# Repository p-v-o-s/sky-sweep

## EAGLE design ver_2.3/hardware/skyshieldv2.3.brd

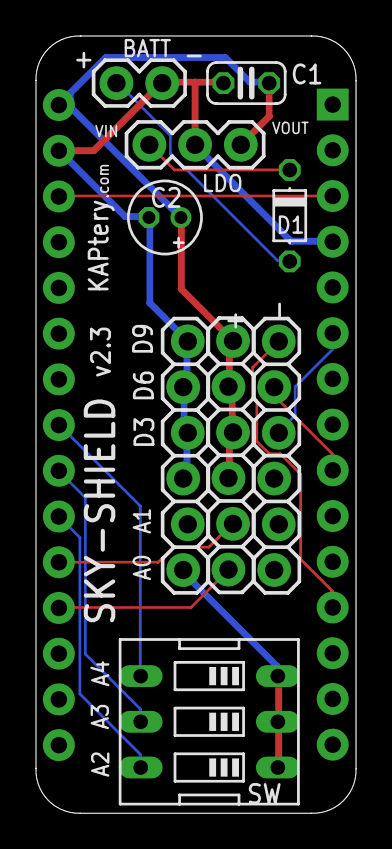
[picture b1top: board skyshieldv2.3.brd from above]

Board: 2 copper layers, 17.8 x 43.2 mm, 11 parts (0 on the bottom side), 13 nets.

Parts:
BATT: 1X02
C1: 0.1µ; C025-024X044
C2: 10µ; E1,8-4
D1: D-5
J1: HEAD15-NOSS
J2: HEAD15-NOSS-1
JP1, JP2, JP3: 1X06_LOCK
LDO-5V: LF50ABV-DG; 1X03
SW2: EDG-03

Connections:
A0: J2.12, JP2.1
A1: J2.11, JP2.2
A2: J2.10, SW2.6
A3: J2.9, SW2.5
A4: J2.8, SW2.4
D3: J1.6, JP3.4
D6: J1.9, JP3.5
D9: J1.12, JP3.6
GND: BATT.2, C1.2, C2.-, J1.4, J2.2, JP1.1, JP1.2, JP1.4, JP1.5, JP1.6, LDO-5V.2, SW2.1, SW2.2, SW2.3
unnamed: BATT.1, D1.A
unnamed: D1.C, LDO-5V.3
RESET: J1.3, J2.3
VCC: C1.1, C2.+, J2.1, JP2.4, JP2.5, JP2.6, LDO-5V.1

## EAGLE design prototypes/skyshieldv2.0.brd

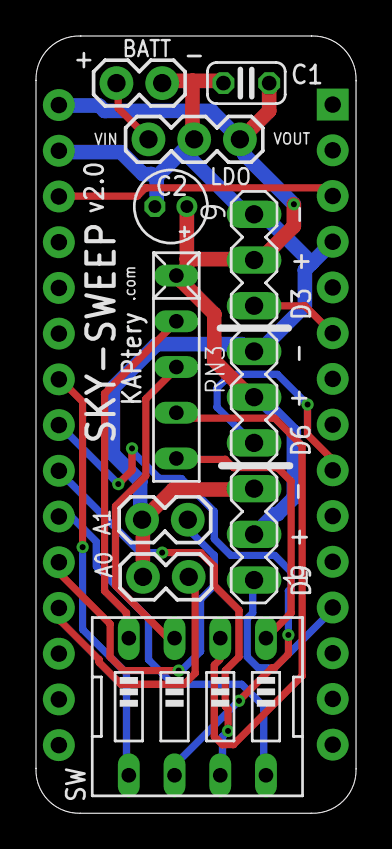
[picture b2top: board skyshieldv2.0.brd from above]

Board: 2 copper layers, 17.8 x 43.2 mm, 11 parts (0 on the bottom side), 17 nets.

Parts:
BATT: 1X02
C1: 0.1µ; C025-024X044
C2: 10µ; E1,8-4
CHDKA: 1X02
CHDKB: 1X02
J1: HEAD15-NOSS
J2: HEAD15-NOSS-1
LDO-5V: LF50ABV-DG; 1X03
RN3: RN-5
SV4: MA09-1
SW1: EDG-04

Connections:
A0: CHDKA.2, J2.12
A1: CHDKB.2, J2.11
A2: J2.10, SW1.8
A3: J2.9, SW1.7
A4: J2.8, SW1.6
A5: J2.7, SW1.5
D3: J1.6, SV4.7
D6: J1.9, SV4.4
D9: J1.12, SV4.1
GND: BATT.2, C1.2, C2.-, CHDKA.1, CHDKB.1, J1.4, J2.2, LDO-5V.2, SV4.3, SV4.6, SV4.9
unnamed: RN3.2, SW1.4
unnamed: BATT.1, LDO-5V.3
unnamed: RN3.3, SW1.3
unnamed: RN3.4, SW1.2
unnamed: RN3.5, SW1.1
RESET: J1.3, J2.3
VCC: C1.1, C2.+, J2.1, LDO-5V.1, RN3.1, SV4.2, SV4.5, SV4.8

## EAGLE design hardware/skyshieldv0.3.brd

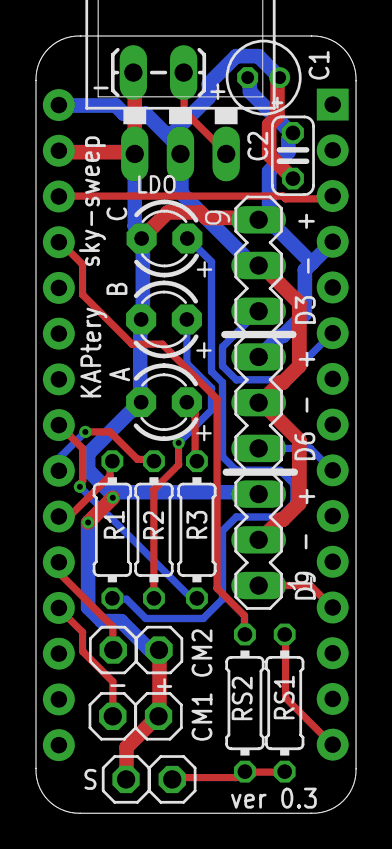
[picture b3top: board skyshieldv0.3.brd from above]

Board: 2 copper layers, 17.8 x 43.2 mm, 21 parts (0 on the bottom side), 18 nets.

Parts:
C1: 0.1µ; C025-024X044
C2: 10µ; E1,8-4
CHDK1A, CHDK1B, CHDK2A, CHDK2B: 1X01
IC1: LD117AV; TO220L1
J1: HEAD15-NOSS
J2: HEAD15-NOSS-1
JP1: BATT; 1X02_LOCK_LONGPADS
LED, LED1, LED2: POWERLED; LED3MM
R1, R2, R3: 10K; 0204/7
RS1: 100; 0204/7
RS2: 10K; 0204/7
SV4: MA09-1
SW1A, SW1B: 1X01

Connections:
+5V: J2.4, RS2.1
A0: CHDK1A.1, J2.12
A1: CHDK2A.1, J2.11
A2: J2.10, R1.1
A3: J2.9, R2.1
A4: J2.8, R3.1
D3: J1.6, SV4.7
D6: J1.9, SV4.4
D9: J1.12, SV4.1
D12/MISO: J1.15, RS1.2
GND: C1.2, C2.-, CHDK1B.1, CHDK2B.1, IC1.1, J1.4, J2.2, JP1.2, LED.K, LED1.K, LED2.K, SV4.3, SV4.6, SV4.9, SW1B.1
unnamed: LED2.A, R3.2
unnamed: LED1.A, R2.2
unnamed: LED.A, R1.2
unnamed: RS1.1, RS2.2, SW1A.1
unnamed: IC1.3, JP1.1
RESET: J1.3, J2.3
VCC: C1.1, C2.+, IC1.2, J2.1, SV4.2, SV4.5, SV4.8

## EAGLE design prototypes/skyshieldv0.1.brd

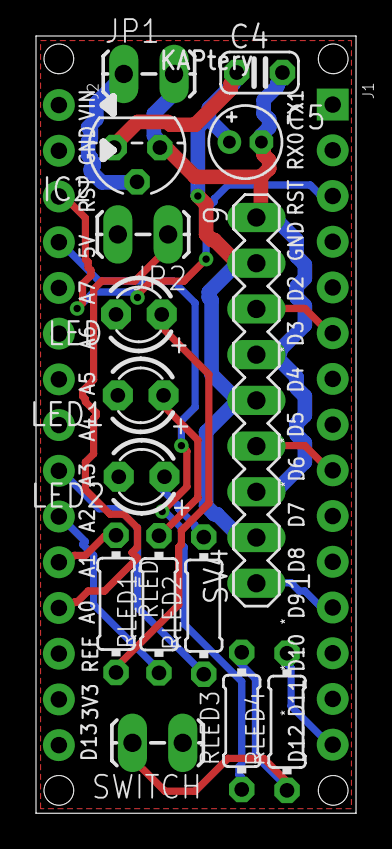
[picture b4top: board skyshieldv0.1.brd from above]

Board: 2 copper layers, 17.8 x 43.2 mm, 18 parts (1 on the bottom side), 18 nets.

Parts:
C4: 0.1µ; C025-024X044
C5: 10µ; E1,8-4
IC2: MCP1702-5; TO92
J1: HEAD15-NOSS
J2: HEAD15-NOSS-1
JP1: BATT; 1X02_LOCK_LONGPADS
JP2: USB; 1X02_LOCK_LONGPADS
LED, LED1, LED2: POWERLED; LED3MM
RLED, RLED1, RLED2, RLED3, RLED4: 1.5K; 0204/7
SV4: MA09-1
SWITCH: adafruit; 1X02_LOCK_LONGPADS
U$54: FIDUCIAL1X2; FIDUCIAL-1X2

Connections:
+5V: J2.4, RLED3.1
A0: J2.11, RLED.1
A1: J2.10, RLED1.1
A3: J2.9, RLED2.1
COM: J1.4, J2.2, JP2.2, LED.K, LED1.K, LED2.K, SWITCH.1
D3: J1.6, SV4.7
D6: J1.9, SV4.4
D9: J1.12, SV4.1
D12/MISO: J1.15, RLED4.2
GND: C4.2, C5.-, IC2.1, JP1.2, SV4.3, SV4.6, SV4.9
unnamed: LED2.A, RLED2.2
unnamed: LED1.A, RLED1.2
unnamed: LED.A, RLED.2
unnamed: RLED3.2, RLED4.1, SWITCH.2
unnamed: J2.12, JP2.1
PWR: IC2.2, JP1.1
RESET: J1.3, J2.3
VCC: C4.1, C5.+, IC2.3, SV4.2, SV4.5, SV4.8

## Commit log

2015-04-03 update ;

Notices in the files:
parts and their libraries:
SparkFun-Connectors: Licensing: Creative Commons ShareAlike 4.0 International - https://creativecommons.org/licenses/by-sa/4.0
